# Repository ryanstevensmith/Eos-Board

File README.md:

# Eos-Board
 The Eos altimeter board for altimeter development within HRG
 
 Due to be built and tested in October 2021

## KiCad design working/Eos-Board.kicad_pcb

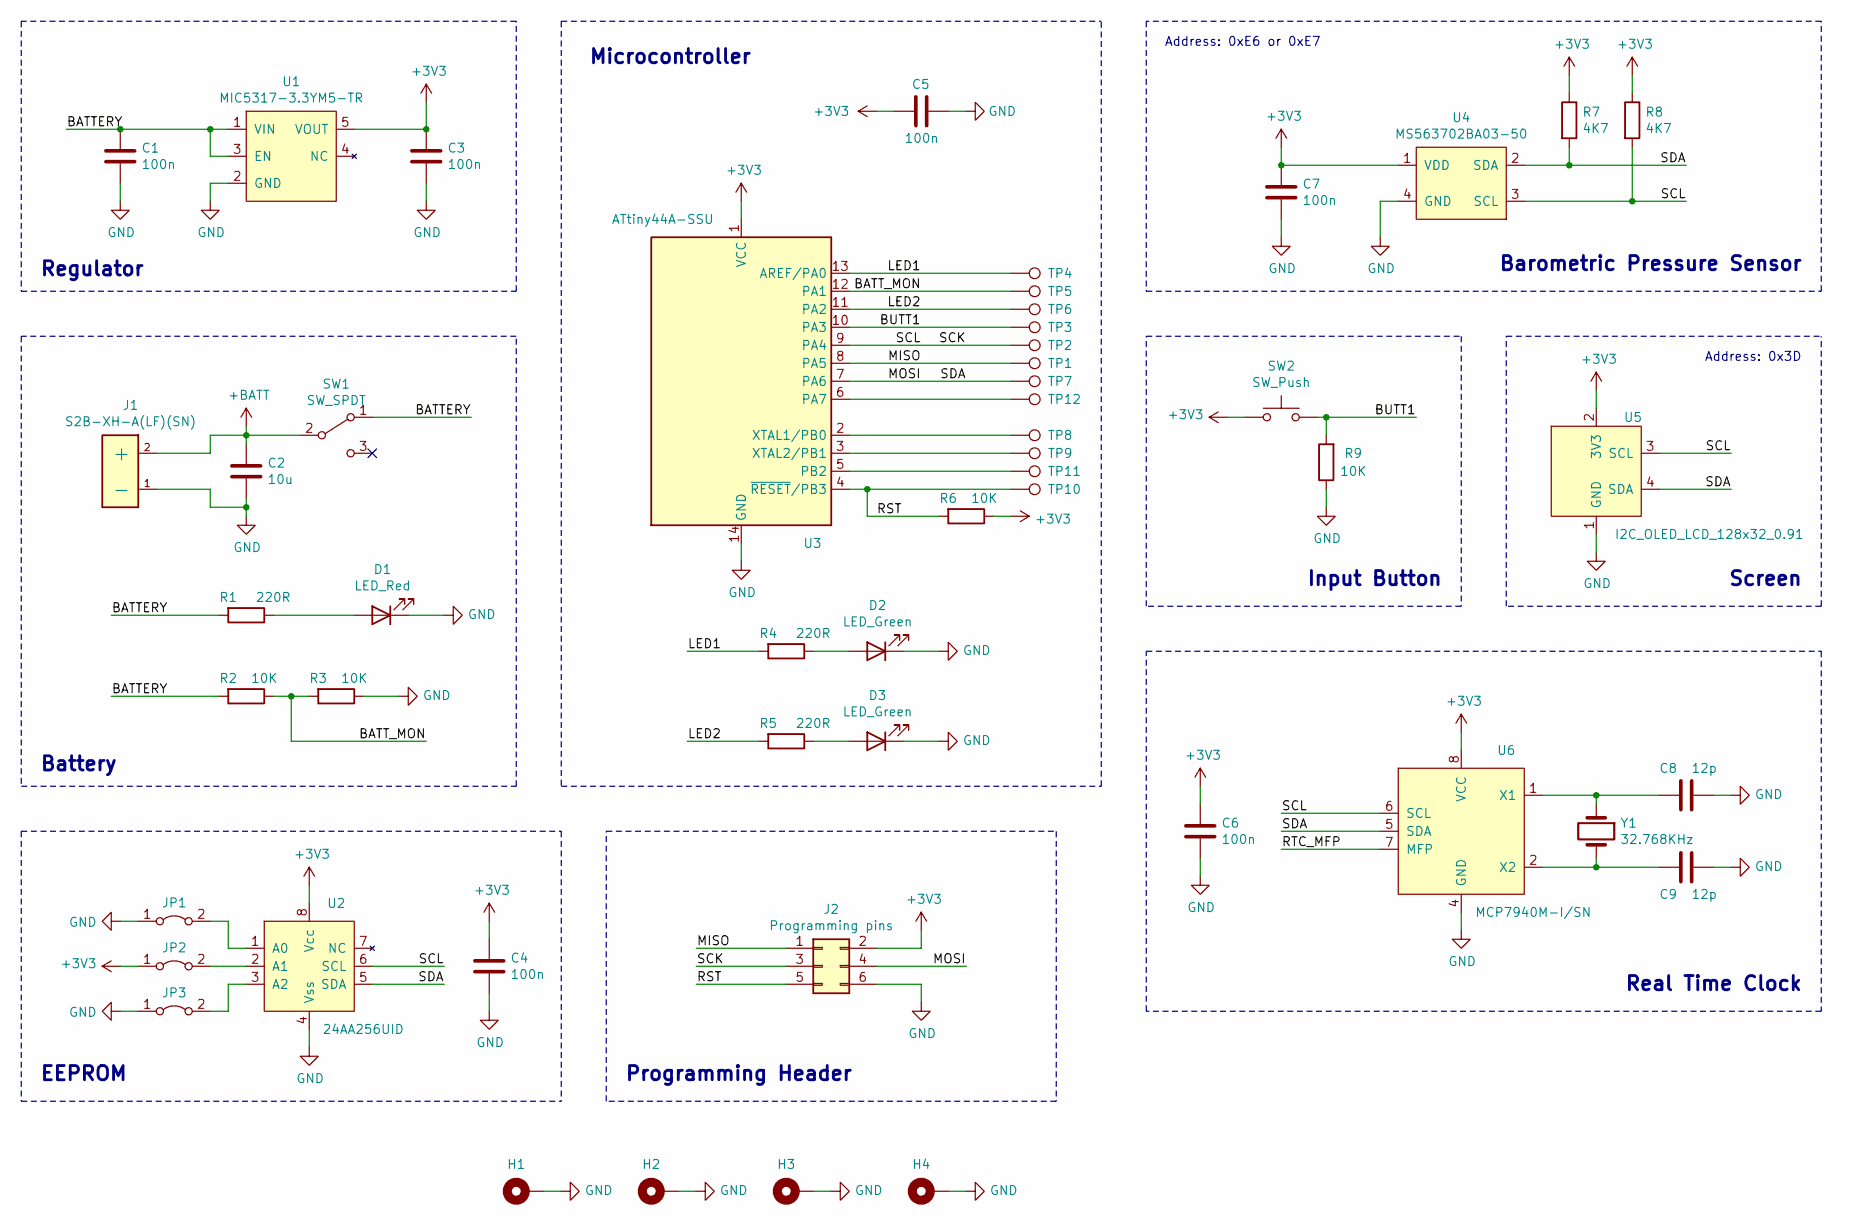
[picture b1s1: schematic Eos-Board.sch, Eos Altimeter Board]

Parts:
C1, C3, C4, C5, C6, C7: 100n; C_0603_1608Metric; Part Number C0603C104J5RACTU
C2: 10u; C_1206_3216Metric; Part Number C1206C106M3PACTU
C8, C9: 12p; C_0603_1608Metric; Part Number C0603C120K5RACTU
D1: LED_Red; LED_0603_1608Metric; Part Number APT1608SRCPRV
D2, D3: LED_Green; LED_0603_1608Metric; Part Number APT1608SGC
H1, H2, H3, H4: MountingHole_Pad; MountingHole_3.2mm_M3_Pad_Via
J1: S2B-XH-A(LF)(SN); Part Number S2B-XH-A(LF)(SN)
J2: Programming pins; PinHeader_2x03_P2.54mm_Vertical
JP1, JP2, JP3: Jumper_2_Bridged; SolderJumper-2_P1.3mm_Bridged_RoundedPad1.0x1.5mm
R1, R4, R5: 220R; R_0603_1608Metric; Part Number CRCW0603220RFKEAHP
R2, R3, R6, R9: 10K; R_0603_1608Metric; Part Number CRCW060310K0FKEAHP
R7, R8: 4K7; R_0603_1608Metric; Part Number CRCW06034K70FKEAHP
SW1: SW_SPDT; CAS-120-B-type; Part Number CAS-120TB
SW2: SW_Push; SW_SPST_TL3342; Part Number TL3342F160QG
TP1, TP2, TP3, TP4, TP5, TP6, TP7, TP8, TP9, TP10, TP11, TP12: TestPoint; TestPoint_THTPad_D2.0mm_Drill1.0mm
U1: MIC5317-3.3YM5-TR; SOT-23-5; Part Number MIC5317-3.3YM5-TR
U2: 24AA256UID; SOIC-8_3.9x4.9mm_P1.27mm; Part Number 24AA256UID-I/SN
U3: ATtiny44A-SSU; SOIC-14_3.9x8.7mm_P1.27mm
U4: MS563702BA03-50; MS5637-02BA03; Part_Number MS563702BA03-50
U5: I2C_OLED_LCD_128x32_0.91; I2C_128x32_OLED_LCD; Part Number n/a
U6: MCP7940M-I/SN; SOIC-8_3.9x4.9mm_P1.27mm; Part_Number MCP7940M-I/SN
Y1: 32.768KHz; Crystal_DS26_D2.0mm_L6.0mm_Horizontal; Part Number R26-32.768- 12.5

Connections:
+3V3: C3.1, C4.1, C5.1, C6.1, C7.1, J2.2, JP2.1 (A), R6.1, R7.1, R8.1, SW2.1, U1.5 (VOUT), U2.8 (Vcc), U3.1 (VCC), U4.1 (VDD), U5.2 (3V3), U6.8 (VCC)
+BATT: C2.1, J1.2 (+), SW1.2 (B)
/BATTERY: C1.1, R1.2, R2.2, SW1.1 (A), U1.1 (VIN), U1.3 (EN)
/BATT_MON: R2.1, R3.2, TP5.1, U3.12 (PA1)
/BUTT1: R9.2, SW2.2, TP3.1, U3.10 (PA3)
/LED1: R4.2, TP4.1, U3.13 (AREF/PA0)
/LED2: R5.2, TP6.1, U3.11 (PA2)
/MISO: J2.1, TP1.1, U3.8 (PA5)
/MOSI: J2.4, R7.2, TP7.1, U2.5 (SDA), U3.7 (PA6), U4.2 (SDA), U5.4 (SDA), U6.5 (SDA)
/RST: J2.5, R6.2, TP10.1, U3.4 (~RESET~/PB3)
/RTC_MFP: U6.7 (MFP)
/SCK: J2.3, R8.2, TP2.1, U2.6 (SCL), U3.9 (PA4), U4.3 (SCL), U5.3 (SCL), U6.6 (SCL)
GND: C1.2, C2.2, C3.2, C4.2, C5.2, C6.2, C7.2, C8.1, C9.1, D1.1 (K), D2.1 (K), D3.1 (K), H1.1, H2.1, H3.1, H4.1, J1.1 (-), J2.6, JP1.1 (A), JP3.1 (A), R3.1, R9.1, U1.2 (GND), U2.4 (Vss), U3.14 (GND), U4.4 (GND), U5.1 (GND), U6.4 (GND)
unnamed: C8.2, U6.1 (X1), Y1.1
unnamed: C9.2, U6.2 (X2), Y1.2
unnamed: D1.2 (A), R1.1
unnamed: D2.2 (A), R4.1
unnamed: D3.2 (A), R5.1
unnamed: JP1.2 (B), U2.1 (A0)
unnamed: JP2.2 (B), U2.2 (A1)
unnamed: JP3.2 (B), U2.3 (A2)
unnamed: TP8.1, U3.2 (XTAL1/PB0)
unnamed: TP9.1, U3.3 (XTAL2/PB1)
unnamed: TP11.1, U3.5 (PB2)
unnamed: TP12.1, U3.6 (PA7)

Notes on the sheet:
Address: 0xE6 or 0xE7
Address: 0x3D
Regulator
Battery
EEPROM
Programming Header
Microcontroller
Barometric Pressure Sensor
Screen
Real Time Clock
Input Button

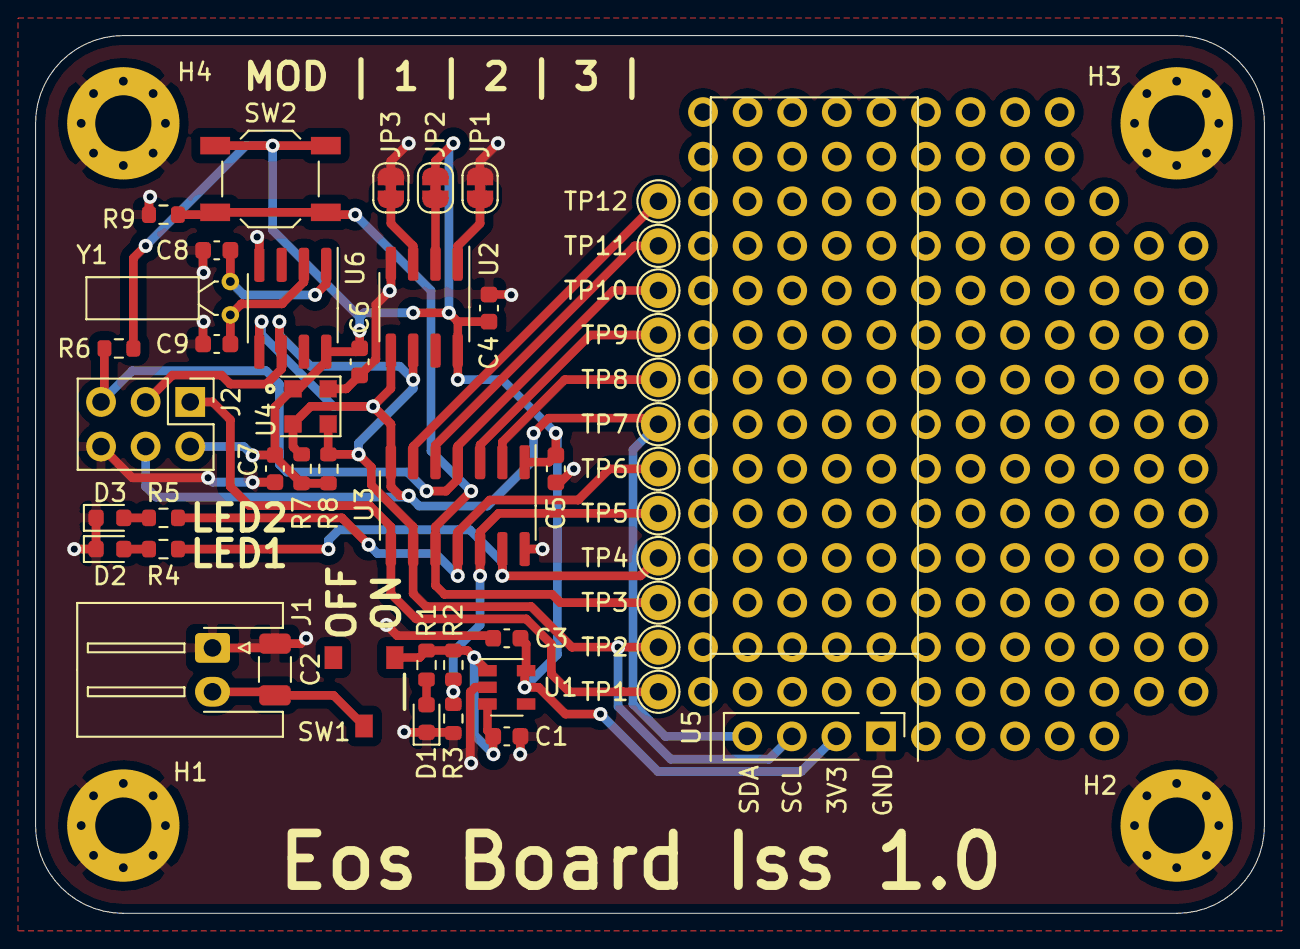
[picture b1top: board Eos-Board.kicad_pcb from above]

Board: 2 copper layers, 70.0 x 50.0 mm, 51 parts (0 on the bottom side), 24 nets.

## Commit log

2021-09-16 First Design Files Release
    Initial Release of design files for the design. There should be enough here for a manufacturing run, but not for mass manufacturing.
2021-09-16 Added schematic image
2021-09-16 Updated Readme
    Added some images of the board render, and an image of the schematic for ease.
2022-02-14 initial software and updated readme
    Added some very basic initial software (nowhere near ready) and updated the readme with images of the first build.
